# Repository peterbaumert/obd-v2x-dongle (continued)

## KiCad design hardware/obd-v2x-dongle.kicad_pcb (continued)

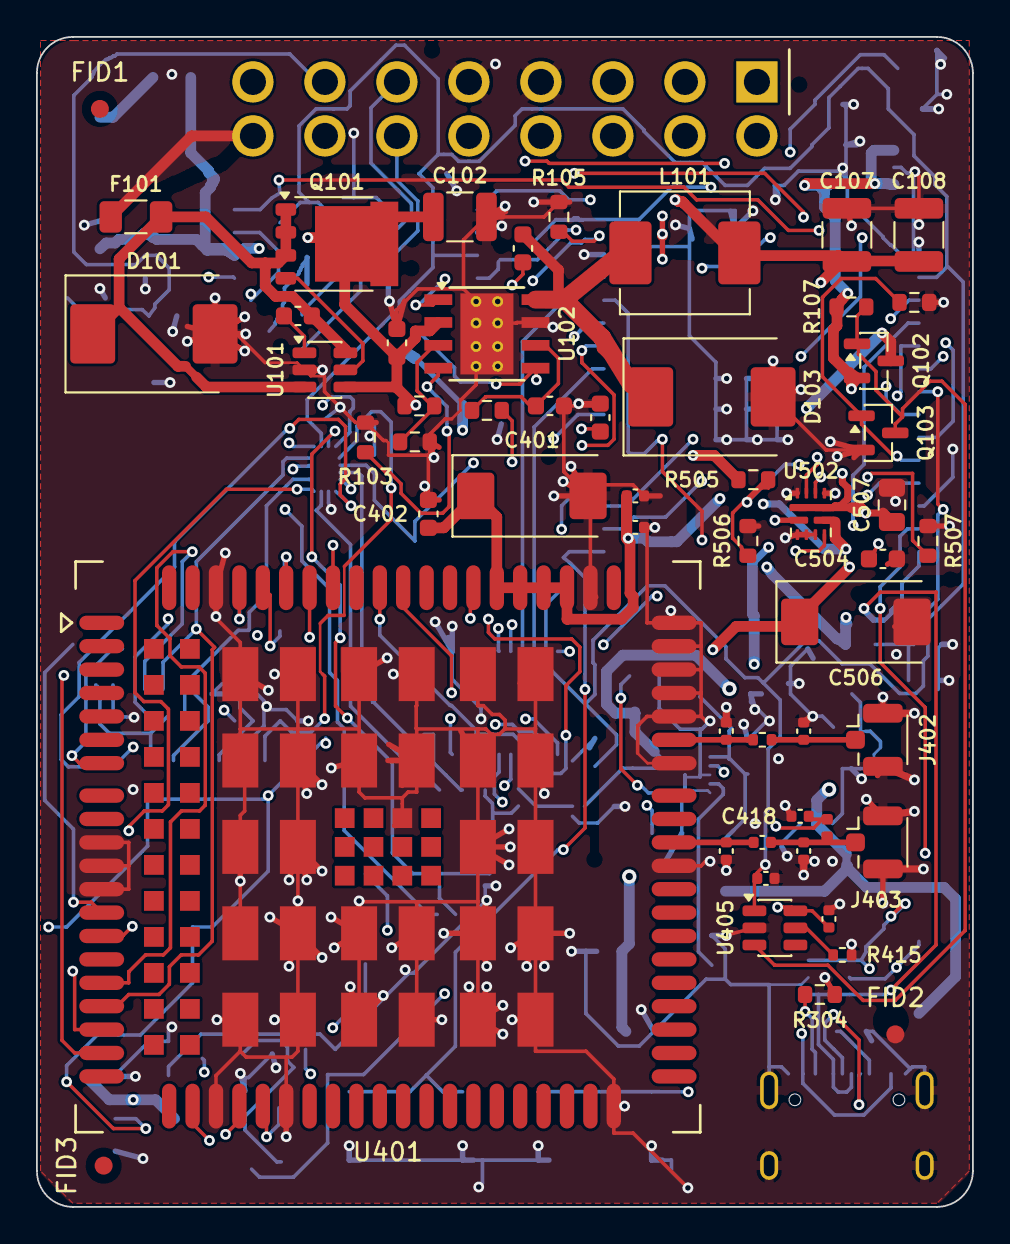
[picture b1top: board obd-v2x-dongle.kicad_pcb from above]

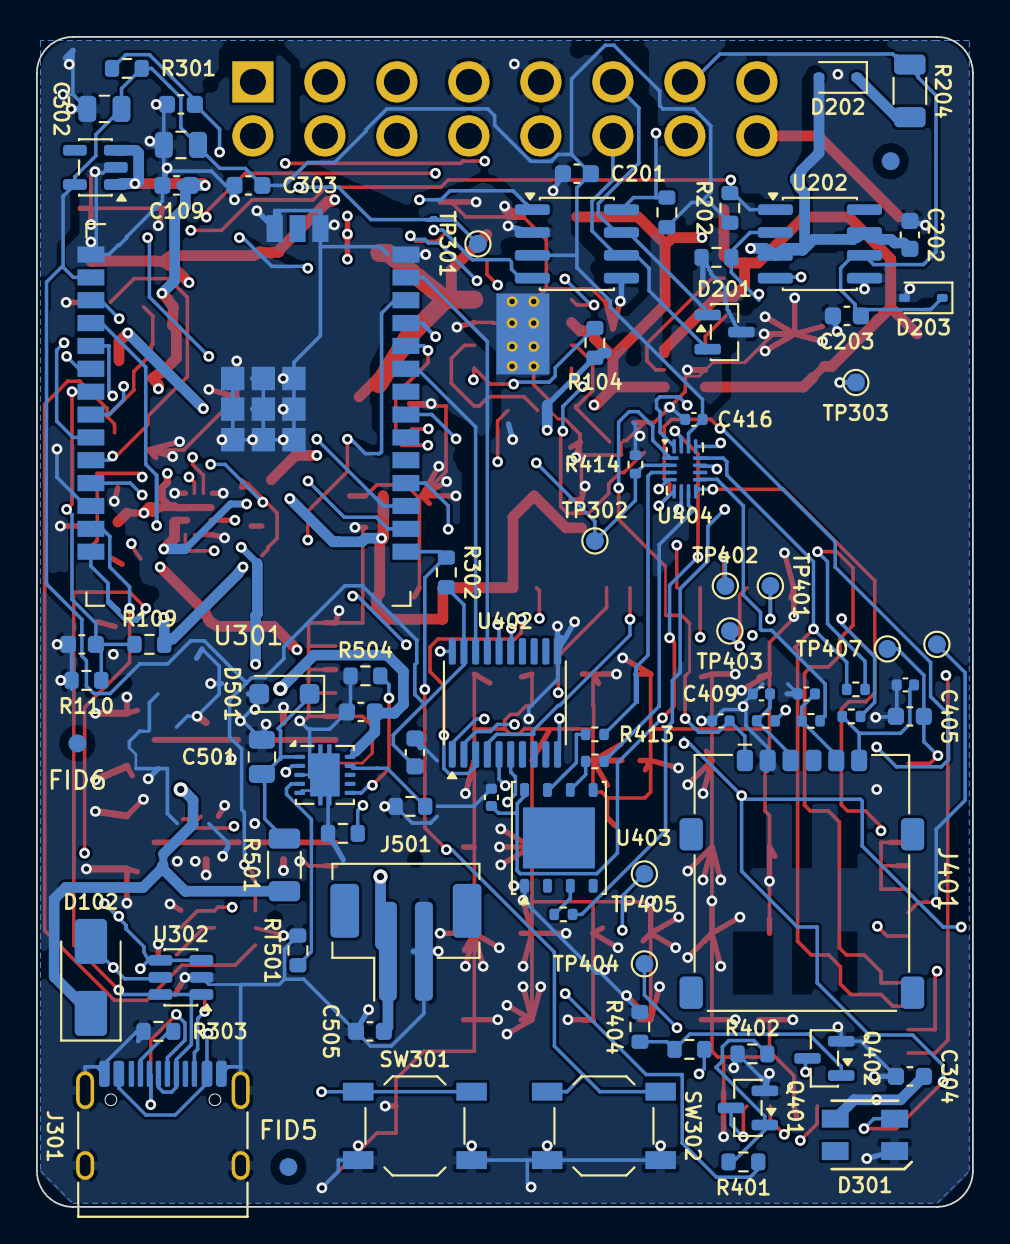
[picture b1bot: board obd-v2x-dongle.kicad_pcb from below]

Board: 4 copper layers, 52.0 x 65.0 mm, 138 parts (83 on the bottom side), 96 nets.

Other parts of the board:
FID1, FID2, FID3, FID4, FID5, FID6: Fiducial; Fiducial_1mm_Mask2mm

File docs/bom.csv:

"Reference","Value","Footprint","MPN","Manufacturer","LCSC","Qty","DNP"
"C101,C104,C111,C201,C303,C304,C402,C405,C406","100nF","Capacitor_SMD:C_0603_1608Metric","","","","9",""
"C102","10uF 50V","Capacitor_SMD:C_1210_3225Metric","","","","1",""
"C103,C202","100nF 50V","Capacitor_SMD:C_0603_1608Metric","","","","2",""
"C105","5.6nF","Capacitor_SMD:C_0603_1608Metric","","","","1",""
"C106","47pF","Capacitor_SMD:C_0603_1608Metric","","","","1",""
"C107,C108","47uF 10V","Capacitor_SMD:C_1210_3225Metric","","","","2",""
"C109,C301,C502,C505","1uF","Capacitor_SMD:C_0603_1608Metric","","","","4",""
"C110,C302,C507","10uF","Capacitor_SMD:C_0805_2012Metric","","","","3",""
"C203","220pF 50V","Capacitor_SMD:C_0603_1608Metric","","","","1",""
"C401","220uF 6.3V","Capacitor_Tantalum_SMD:CP_EIA-7343-31_Kemet-D","T495D227K006ATE100","Kemet","C2798131","1",""
"C403,C407,C408,C409","33pF","Capacitor_SMD:C_0402_1005Metric","","","","4",""
"C404","10pF","Capacitor_SMD:C_0402_1005Metric","","","","1",""
"C410,C415,C416,C419,C420","100nF","Capacitor_SMD:C_0402_1005Metric","","","","5",""
"C411,C412,C413,C414","DNP","Capacitor_SMD:C_0402_1005Metric","","","","4","DNP"
"C417,C418","33pF","Capacitor_SMD:C_0402_1005Metric","0402CG330J500NT","FH","C1562","2",""
"C501","1uF 50V","Capacitor_SMD:C_0805_2012Metric","","","","1",""
"C504","10nF","Capacitor_SMD:C_0603_1608Metric","","","","1",""
"C506","220uF","Capacitor_Tantalum_SMD:CP_EIA-7343-31_Kemet-D","T495D227K006ATE100","KEMET","C2798131","1",""
"D101","SMCJ33CA","Diode_SMD:D_SMC","SMCJ33CA","Littelfuse","C310048","1",""
"D102","SS14","Diode_SMD:D_SMA","SS14","MDD","C2480","1",""
"D103","B560C","Diode_SMD:D_SMC","B560C-13-F","Diodes Inc","C85100","1",""
"D201","NUP2105L","Package_TO_SOT_SMD:SOT-23","SZNUP2105LT1G","onsemi","C233494","1",""
"D202","B0540WS","Diode_SMD:D_SOD-323","B0540WS-7","Diodes Inc","C52754523","1",""
"D203","PESD1LIN","Diode_SMD:D_SOD-323","PESD1LIN,115","Nexperia","C58901","1",""
"D301","SK6812MINI-HS","obd-v2x:LED_SK6812MINI-HS_3.7x3.5mm","SK6812MINI-HS","OPSCO","C2922787","1",""
"D501","SMF24A","Diode_SMD:D_SOD-123F","SMF24A","Littelfuse","C315999","1",""
"F101","2A slow","Fuse:Fuse_1206_3216Metric","0466002.NRHF","Littelfuse","C3105","1",""
"J201","OBD2_J1962_Plug","obd-v2x:OBD2_J1962_Plug_PCB","CR-PG001 (OBD2 male 90deg PCB, hand-fitted)","Jiatel or equivalent","","1",""
"J301","USB-C","Connector_USB:USB_C_Receptacle_HRO_TYPE-C-31-M-12","TYPE-C-31-M-12","HRO","C165948","1",""
"J401","Nano-SIM","Connector_Card:nanoSIM_GCT_SIM8060-6-0-14-00","SIM8060-6-0-14-00-A","GCT","C6296715","1",""
"J402","U.FL LTE main","Connector_Coaxial:U.FL_Hirose_U.FL-R-SMT-1_Vertical","U.FL-R-SMT-1(10)","Hirose","C88373","1",""
"J403","U.FL GNSS","Connector_Coaxial:U.FL_Hirose_U.FL-R-SMT-1_Vertical","U.FL-R-SMT-1(10)","Hirose","C88373","1",""
"J501","Battery 1S","Connector_JST:JST_PH_B2B-PH-SM4-TB_1x02-1MP_P2.00mm_Vertical","B2B-PH-SM4-TB(LF)(SN)","JST","C160352","1",""
"L101","6.8uH 4.5A","Inductor_SMD:L_Sunlord_MWSA0605S","MWSA0605S-6R8MT","Sunlord","C408466","1",""
"L401","27nH","Inductor_SMD:L_0402_1005Metric","LQG15HS27NJ02D","Murata","C12669","1",""
"Q101","PSMN7R0-60YS","Package_TO_SOT_SMD:LFPAK56","PSMN7R0-60YS,115","Nexperia","C478143","1",""
"Q102","AO3401A","Package_TO_SOT_SMD:SOT-23","AO3401A","AOS","C15127","1",""
"Q103","2N7002","Package_TO_SOT_SMD:SOT-23","2N7002","onsemi","C8545","1",""
"Q401,Q402","MMBT3904","Package_TO_SOT_SMD:SOT-23","MMBT3904","onsemi","C20526","2",""
"R101","470k","Resistor_SMD:R_0603_1608Metric","","","","1",""
"R102","120k","Resistor_SMD:R_0603_1608Metric","","","","1",""
"R103","162k","Resistor_SMD:R_0603_1608Metric","","","","1",""
"R104","37.4k","Resistor_SMD:R_0603_1608Metric","","","","1",""
"R105,R110,R201,R301,R302","10k","Resistor_SMD:R_0603_1608Metric","","","","5",""
"R106","12k","Resistor_SMD:R_0603_1608Metric","","","","1",""
"R107,R108,R109,R203","100k","Resistor_SMD:R_0603_1608Metric","","","","4",""
"R202,R401,R403","4.7k","Resistor_SMD:R_0603_1608Metric","","","","3",""
"R204","510 0.5W","Resistor_SMD:R_1206_3216Metric","","","","1",""
"R303,R304","5.1k","Resistor_SMD:R_0603_1608Metric","","","","2",""
"R402,R404","47k","Resistor_SMD:R_0603_1608Metric","","","","2",""
"R405,R406,R407,R411,R412,R413","22R","Resistor_SMD:R_0402_1005Metric","","","","6",""
"R408","15k","Resistor_SMD:R_0402_1005Metric","","","","1",""
"R409","0R","Resistor_SMD:R_0402_1005Metric","","","","1",""
"R414","100k","Resistor_SMD:R_0402_1005Metric","","","","1",""
"R415","232k","Resistor_SMD:R_0402_1005Metric","","","","1",""
"R501","33R 0.5W","Resistor_SMD:R_1206_3216Metric","","","","1",""
"R502","4.3k","Resistor_SMD:R_0603_1608Metric","","","","1",""
"R503","24k 1%","Resistor_SMD:R_0603_1608Metric","","","","1",""
"R504,R505","82k 1%","Resistor_SMD:R_0603_1608Metric","","","","2",""
"R506","10k 1%","Resistor_SMD:R_0603_1608Metric","","","","1",""
"R507","30.1k 1%","Resistor_SMD:R_0603_1608Metric","","","","1",""
"RT501","10k NTC","Resistor_SMD:R_0603_1608Metric","SDNT1608X103F3435FTF","Sunlord","C525660","1",""
"SW301","RESET","Button_Switch_SMD:SW_SPST_TL3342","TL3342F450QG","E-Switch","C2886897","1",""
"SW302","BOOT","Button_Switch_SMD:SW_SPST_TL3342","TL3342F450QG","E-Switch","C2886897","1",""
"TP301","UART0_TX","TestPoint:TestPoint_Pad_D1.0mm","","","","1",""
"TP302","SIM_SEL","TestPoint:TestPoint_Pad_D1.0mm","","","","1",""
"TP303","GND","TestPoint:TestPoint_Pad_D1.0mm","","","","1",""
"TP401","LTE_USB_VBUS","TestPoint:TestPoint_Pad_D1.0mm","","","","1",""
"TP402","LTE_USB_DP","TestPoint:TestPoint_Pad_D1.0mm","","","","1",""
"TP403","LTE_USB_DM","TestPoint:TestPoint_Pad_D1.0mm","","","","1",""
"TP404","LTE_USB_BOOT","TestPoint:TestPoint_Pad_D1.0mm","","","","1",""
"TP405","LTE_DBG_TXD","TestPoint:TestPoint_Pad_D1.0mm","","","","1",""
"TP406","LTE_DBG_RXD","TestPoint:TestPoint_Pad_D1.0mm","","","","1",""
"TP407","LTE_1V8","TestPoint:TestPoint_Pad_D1.0mm","","","","1",""
"U101","LM74700-Q1","Package_TO_SOT_SMD:SOT-23-6","LM74700QDBVRQ1","TI","C2941042","1",""
"U102","TPS54360DDA","Package_SO:TI_SO-PowerPAD-8_ThermalVias","TPS54360DDAR","TI","C44377","1",""
"U103","TLV75733PDBV","Package_TO_SOT_SMD:SOT-23-5","TLV75733PDBVR","TI","C485517","1",""
"U201","TCAN334","Package_SO:SOIC-8_3.9x4.9mm_P1.27mm","TCAN334DR","TI","C2871143","1",""
"U202","TJA1021T/20","Package_SO:SOIC-8_3.9x4.9mm_P1.27mm","TJA1021T/20/CM,118","NXP","C128810","1",""
"U301","ESP32-C5-WROOM-1U-N16R8","obd-v2x:ESP32-C5-WROOM-1U","ESP32-C5-WROOM-1U-N16R8-V1.2","Espressif","C54951857","1",""
"U302","USBLC6-2SC6","Package_TO_SOT_SMD:SOT-23-6","USBLC6-2SC6","ST","C2827654","1",""
"U401","EC200U-EU","obd-v2x:Quectel_EC200U","EC200UEUAA-N05-SGNSA","Quectel","C2942341","1",""
"U402","TXS0108EPW","Package_SO:TSSOP-20_4.4x6.5mm_P0.65mm","TXS0108EPWR","TI","C17206","1",""
"U403","eSIM MFF2","Package_SON:WSON-8-1EP_6x5mm_P1.27mm_EP3.4x4mm","MFF2 eSIM, optional (DNP)","","","1","DNP"
"U404","FSA2567UMX","Package_DFN_QFN:UQFN-16_1.8x2.6mm_P0.4mm","FSA2567UMX","onsemi","C357761","1",""
"U405","TPS2552DBVR-1","Package_TO_SOT_SMD:SOT-23-6","TPS2552DBVR-1","TI","C140331","1",""
"U501","BQ25171-Q1","Package_SON:Texas_DRC0010J","BQ25171QWDRCRQ1","Texas Instruments","C2861221","1",""
"U502","TPS2121","Package_DFN_QFN:Texas_VQFN-HR-12_2x2.5mm_P0.5mm","TPS2121RUXR","Texas Instruments","C485916","1",""

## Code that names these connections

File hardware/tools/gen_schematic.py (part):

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
    sh.text('Input protection: fuse, TVS, ideal-diode reverse protection', g(5), g(6), 1.5, True)
    F = sh.part('Device:Fuse', 'F101', '2A slow', 'Fuse:Fuse_1206_3216Metric', g(14), y0, 90, fields=H(g(14), y0))
    sh.glabel('OBD_VBAT', F.out(1, 1), 'L', 'input')
    sh.w(F.out(1, 1), F[1])

    xt = g(19)
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    sh.w(C[1], U['VCAP'])
    sh.w(C[2], (xv, y0))
    sh.w(U['EN'], (xv - g(2), U['EN'][1]))
    sh.label('VBAT_F', (xv - g(2), U['EN'][1]), 'L')
    sh.label('VBAT_F', (xt + g(3), y0), 'R')
    # main line, input side
    sh.w(F[2], (xt, y0), (xt + g(3), y0), (xv, y0), (xa, y0), Q['S'])
    sh.rail('VIN_PROT', (xc + g(3), y0))
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    Dv.fields = {'ref': (xu + 2.54, Dv.y - 1.27, 'left'), 'val': (xu + 2.54, Dv.y + 1.27, 'left')}
    sh.w(Dv['K'], (xu, y0))
    sh.w(Dv['A'], (xu, Dv['A'][1] - g(1)), (xu - g(1), Dv['A'][1] - g(1)))
    sh.glabel('VBUS_USB', (xu - g(1), Dv['A'][1] - g(1)), 'L', 'input')

    # input caps
    xc1, xc2 = xu + g(4), xu + g(9)
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    R3.fields = {'ref': (xrt - 2.032, R3.y - 1.27, 'right'), 'val': (xrt - 2.032, R3.y + 1.27, 'right')}
    sh.gnd(R3[2])
    # EN divider (labelled)
    sh.label('BUCK_EN', B['EN'], 'L', stub=1)
    xen = g(62)
    R1 = rv(sh, 'Device:R', 'R101', '470k', R0603, xen, y0 + g(9))
    sh.rail('VIN_PROT', R1[1])
    R2 = rv(sh, 'Device:R', 'R102', '120k', R0603, xen, R1[2][1] + g(2))
    sh.w(R1[2], R2[1])
    sh.label('BUCK_EN', (xen, R1[2][1] + g(1)), 'R', stub=0)
    sh.gnd(R2[2])
    # BOOT cap (horizontal, above) between BOOT and SW
    x1 = B['BOOT'][0] + g(1)
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    Rf2 = rv(sh, 'Device:R', 'R105', '10k', R0603, xf, Rf1[2][1] + g(2))
    sh.w(Rf1[2], Rf2[1])
    sh.gnd(Rf2[2])
    sh.label('BUCK_FB', (xf, Rf1[2][1] + g(1)), 'L', stub=0)
    sh.w((xf, Rf1[2][1] + g(1)), (xf - g(1), Rf1[2][1] + g(1)))
    sh.labels[-1] = ('label', 'BUCK_FB', (xf - g(1), Rf1[2][1] + g(1)), 180, None)
    sh.label('BUCK_FB', B['FB'], 'R', stub=1)
    # output caps
    xo1, xo2 = xf + g(5), xf + g(11)
    cap_to_gnd(sh, 'C107', '47uF 10V', C1210, xo1, yo, 2)
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    sh.w(L[2], (xf, yo), (xo1, yo), (xo2, yo), (xo2 + g(3), yo))
    sh.rail('VBUCK_3V8', (xo2 + g(3), yo))   # -> TPS2121 IN1 (battery sheet); loads are on VSYS_3V8
    # compensation (COMP -> R106 -> C105 -> GND, C106 || to GND), labelled
    sh.label('BUCK_COMP', B['COMP'], 'R', stub=1)
    yc = B['GND'][1] + g(5)
    xcmp = XB - g(2)
    sh.label('BUCK_COMP', (xcmp, yc), 'L')
    sh.w((xcmp, yc), (xcmp + g(6), yc))
    Rc = rv(sh, 'Device:R', 'R106', '12k', R0603, xcmp + g(2), yc)
    Cc = rv(sh, 'Device:C', 'C105', '5.6nF', C0603, xcmp + g(2), Rc[2][1] + g(1))
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    sh.w(Rg[2], (Rg[2][0], gt[1] + (g(1) if gt[1] > ys else -g(1))))
    yg = Rg[2][1] + g(1)
    sh.w(Rg[2], (Rg[2][0], yg), (gt[0], yg), gt) if gt[1] > ys else None
    sh.glabel('LTE_PWR_ON_N', (Rg[2][0], yg), 'L', 'output', stub=2)    # low while the modem is powered
    Qn = sh.part('Transistor_FET:2N7002', 'Q103', '2N7002', SOT23, gt[0] - 2.54, yg + g(2) + 5.08, 0,
                 fields={'ref': (gt[0] + 1.27, yg + g(2) + 3.81, 'left'), 'val': (gt[0] + 1.27, yg + g(2) + 6.35, 'left')})
    sh.w((gt[0], yg), Qn['D'])
    sh.gnd(Qn['S'])
    sh.w(Qn['G'], (Qn['G'][0] - g(4), Qn['G'][1]))
    sh.glabel('LTE_PWR_EN', (Qn['G'][0] - g(4), Qn['G'][1]), 'L', 'input')
    Rpd = rv(sh, 'Device:R', 'R108', '100k', R0603, Qn['G'][0] - g(2), Qn['G'][1])
    sh.gnd(Rpd[2])

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    Cs = rv(sh, 'Device:C', 'C111', '100nF', C0603, xs + g(4), yn)
    sh.w((xs, yn), Cs[1], (xs + g(8), yn))
    sh.gnd(Cs[2])
    sh.glabel('VSENSE', (xs + g(8), yn), 'R', 'output')

    # ---------------- power flags
    yf = g(72)
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            sh.gnd(flg[1])
        elif net == 'VBAT_F':
            sh.w(flg[1], (x, yf + g(1)), (x + g(1), yf + g(1)))
            sh.label('VBAT_F', (x + g(1), yf + g(1)), 'R')
        else:
            sh.w(flg[1], (x, yf + g(1)))
            sh.parts.append(None) if False else None
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    sh.text('OBD-II plug (vehicle side)', g(6), g(18), 1.5, True)
    # battery
    sh.w(J['16'], (g(30), J['16'][1]))
    sh.glabel('OBD_VBAT', (g(30), J['16'][1]), 'R', 'output')
    # grounds
    xg = J['5'][0] + g(2)
    sh.w(J['5'], (xg, J['5'][1]))
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    sh.gnd(U['GND'])
    xr = U['TXD'][0]
    sh.w(U['TXD'], (xr + g(3), U['TXD'][1]))
    sh.glabel('CAN_TX', (xr + g(3), U['TXD'][1]), 'R', 'input')
    sh.w(U['RXD'], (xr + g(3), U['RXD'][1]))
    sh.glabel('CAN_RX', (xr + g(3), U['RXD'][1]), 'R', 'output')
    sh.gnd(U['SHDN'], stub=1, rot=90)
    ys = U['STB'][1]
    R = rv(sh, 'Device:R', 'R201', '10k', R0603, xr + g(12), ys - 7.62)
    sh.rail('+3V3', R[1])
    sh.w(U['STB'], (xr + g(12), ys), (xr + g(15), ys))
    sh.glabel('CAN_STB', (xr + g(15), ys), 'R', 'input')
    decap(sh, 'C201', '100nF', C0603, XU + g(8), U['VCC'][1] - g(6), '+3V3')

    # ---------------- K-Line
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    Rx = rv(sh, 'Device:R', 'R202', '4.7k', R0603, xr + g(6), yrx - 7.62)
    sh.rail('+3V3', Rx[1])
    sh.w(K['RXD'], (xr + g(6), yrx), (xr + g(10), yrx))
    sh.glabel('KL_RX', (xr + g(10), yrx), 'R', 'output')
    sh.w(K['TXD'], (xr + g(10), K['TXD'][1]))
    sh.glabel('KL_TX', (xr + g(10), K['TXD'][1]), 'R', 'input')
    ysl = K['~{SLP}'][1]
    sh.w(K['~{SLP}'], (xr + g(6), ysl), (xr + g(10), ysl))
    sh.glabel('KL_SLP_N', (xr + g(10), ysl), 'R', 'input')
    Rs = rv(sh, 'Device:R', 'R203', '100k', R0603, xr + g(6), ysl + g(2))
    sh.w((xr + g(6), ysl), Rs[1])
    sh.gnd(Rs[2])
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    sh.gnd(bot)
    yn = Rb[2][1] + g(1)
    sh.w((xb, yn), (xb - g(3), yn))
    sh.label('ESP_BOOT', (xb - g(3), yn), 'L')
    # LED
    Dl = sh.part('obd-v2x:SK6812MINI-HS', 'D301', 'SK6812MINI-HS', 'obd-v2x:LED_SK6812MINI-HS_3.7x3.5mm', g(98), g(36), 0)
    Dl.fields = {'ref': (g(98) + g(4), g(35), 'left'), 'val': (g(98) + g(4), g(37), 'left')}
    sh.rail('VSYS_3V8', Dl['VDD'])
    sh.gnd(Dl['GND'])
    sh.w(Dl['DIN'], Dl.out('DIN', 2))
    sh.label('LED_DIN', Dl.out('DIN', 2), 'L')
    sh.nc(Dl, 'DOUT')
    decap(sh, 'C304', '100nF', C0603, g(106), g(30), 'VSYS_3V8')

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    J.fields = {'ref': (Jx - g(6), Jy - g(10), 'left'), 'val': (Jx - g(6), Jy - g(9), 'left')}
    xr = J['A4'][0]
    sh.w(J['A4'], (xr + g(8), J['A4'][1]))
    sh.glabel('VBUS_USB', (xr + g(8), J['A4'][1]), 'R', 'output')
    Rc1 = rh(sh, 'Device:R', 'R303', '5.1k', R0603, xr + g(2), J['A5'][1])
    sh.w(J['A5'], Rc1[1])
    sh.gnd(Rc1[2], rot=90)
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    xd = xr + g(2)
    sh.w(J['A7'], (xd, J['A7'][1]), (xd, J['B7'][1]), J['B7'])
    sh.w((xd, J['A7'][1]), (xd + g(3), J['A7'][1]))
    sh.label('USB_DN', (xd + g(3), J['A7'][1]), 'R')
    sh.w(J['A6'], (xd, J['A6'][1]), (xd, J['B6'][1]), J['B6'])
    sh.w((xd, J['B6'][1]), (xd + g(3), J['B6'][1]))
    sh.label('USB_DP', (xd + g(3), J['B6'][1]), 'R')
    sh.nc(J, 'A8')
    sh.nc(J, 'B8')
    sh.w(J['SH'], J['A1'])
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    # ESD
    E = sh.part('Power_Protection:USBLC6-2SC6', 'U302', 'USBLC6-2SC6', 'Package_TO_SOT_SMD:SOT-23-6', g(44), g(62), 0)
    E.fields = {'ref': (g(44) + g(2), g(62) - g(3), 'left'), 'val': (g(44) + g(2), g(62) + g(4), 'left')}
    for pin, net, side in (('1', 'USB_DP', 'L'), ('3', 'USB_DN', 'L'), ('6', 'USB_DP', 'R'), ('4', 'USB_DN', 'R')):
        sh.w(E[pin], E.out(pin, 2))
        sh.label(net, E.out(pin, 2), side)
    sh.w(E['VBUS'], E.out('VBUS', 1))
    sh.glabel('VBUS_USB', E.out('VBUS', 1), 'U', 'input')
    sh.gnd(E['GND'])
    # test points
    sh.text('Test pads: UART0 TX, SIM_SEL (IO12, was RXD0)', g(64), g(56), 1.5, True)
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    sh.gnd((U['10'][0] + g(2), U['10'][1]), rot=90)
    sh.gnd(U['8'])
    # VBAT decoupling
    sh.text('VBAT_LTE bulk/decoupling (close to pins 57-60)', g(3), g(55), 1.27, True)
    decap(sh, 'C401', '220uF 6.3V', 'Capacitor_Tantalum_SMD:CP_EIA-7343-31_Kemet-D', g(5), g(58), 'VBAT_LTE', lib='Device:C_Polarized')
    decap(sh, 'C402', '100nF', C0603, g(13), g(58), 'VBAT_LTE')
    decap(sh, 'C403', '33pF', C0402, g(19), g(58), 'VBAT_LTE')
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                    ('15', 'SIM2_VDD'), ('3', 'SIM2_RST'), ('7', 'SIM2_CLK'), ('11', 'SIM2_DAT')], 'R', 2, set())
    ps = W['2']
    sh.w(ps, (ps[0] - g(2), ps[1]), (ps[0] - g(4), ps[1]))
    sh.glabel('SIM_SEL', (ps[0] - g(4), ps[1]), 'L', 'input')
    Rsel = rv(sh, 'Device:R', 'R414', '100k', R0402, ps[0] - g(2), ps[1])
    Rsel.fields = VL(Rsel.x, Rsel.y)
    sh.gnd(Rsel[2])
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                dnp=True)
    E.fields = {'ref': (XE + g(1), E['8'][1] - g(2.5), 'left'), 'val': (XE + g(1), E['8'][1] - g(1.5), 'left')}
    # series resistors on rows 3 grid apart; each wire drops in its own column to its pin row (no crossings)
    for yr, xc, pin, src, rref in ((g(10), g(62), '7', 'SIM2_RST', 'R413'), (g(13), g(60), '6', 'SIM2_CLK', 'R412'),
                                   (g(16), g(58), '3', 'SIM2_DAT', 'R411')):
        Re = rh(sh, 'Device:R', rref, '22R', R0402, g(52), yr)
        sh.w(Re[2], (xc, yr), (xc, E[pin][1]), E[pin])
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        sh.label(src, (g(51), yr), 'L')
    xv, yv = g(66), g(7.5)
    sh.w(E['8'], (xv, E['8'][1]), (xv, yv))
    sh.label('SIM2_VDD', (xv, yv), 'L')
    Ce = rv(sh, 'Device:C', 'C415', '100nF', C0402, g(70), yv)
    sh.w((xv, yv), Ce[1])
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
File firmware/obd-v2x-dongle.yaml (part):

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modem:
  id: lte
  model: GENERIC
  tx_pin: GPIO23              # IO23 (pin 21) MCU_TX_LTE -> modem RXD
  rx_pin: GPIO24              # IO24 (pin 23) MCU_RX_LTE <- modem TXD
  rts_pin: GPIO26             # IO26 (pin 27) MCU_RTS_LTE -> modem RTS
  cts_pin: GPIO25             # IO25 (pin 26) MCU_CTS_LTE <- modem CTS
  # 921600 instead of the default 115200 (~11 kB/s, too slow for busy roads): the component starts at 115200,
  # switches the EC200U with AT+IPR and remembers the rate. RTS/CTS flow control; the TXS0108E handles this easily.
  baud_rate: 921600
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# components/obd2 (ESPHome's esp32_can does not link on the ESP32-C5). Only active while the engine runs.
obd2:
  id: obd
  tx_pin: GPIO4               # IO4 (pin 17) CAN_TX -> TCAN334
  rx_pin: GPIO5               # IO5 (pin 16) CAN_RX <- TCAN334
  standby_pin: GPIO10         # IO10 (pin 12) TCAN334 STB, high = standby
  bit_rate: 500000
  poll_interval: 250ms        # one request per 250 ms, round robin (speed/RPM twice per round)
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
# ---------------------------------------------------------------- sensors
sensor:
  - platform: adc             # IO1 (pin 7) VSENSE = VIN_PROT / 11 (R109 100k / R110 10k)
    id: car_battery
    name: "Car battery"
    pin: GPIO1
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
